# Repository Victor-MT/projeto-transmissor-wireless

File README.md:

# Projeto Transmissor Wireless

### Sobre o projeto

O projeto em questão foi desenvolvido  com intuito de resolver um desafio proposto em um processo seletivo. A proposta é comunicar dois dispositivos utilizando tecnologia sem fio ou "wireless".
 
Considerando todos os aspectos  do desenvolvimento de uma solução tecnológica, o projeto foi dividido em etapas como definição de requisitos, desenvolvimento de hardware, software e produto final. Todas essas fases, embora pareçam seguir uma ordem em cadeia, foram desenvolvidas de forma iterativa e isso resultou em uma solução que atende todos requisitos solicitados. 

### Sumário
- [Definição de Requisitos](https://github.com/Victor-MT/projeto-transmissor-wireless#defini%C3%A7%C3%A3o-de-requisitos)
- [Arquitetura](https://github.com/Victor-MT/projeto-transmissor-wireless#arquitetura)
- [Hardware](https://github.com/Victor-MT/projeto-transmissor-wireless#hardware)
- [Firmware](https://github.com/Victor-MT/projeto-transmissor-wireless#firmware)
- [Produto Final](https://github.com/Victor-MT/projeto-transmissor-wireless#produto-final)
- [Conclusão](https://github.com/Victor-MT/projeto-transmissor-wireless#conclus%C3%A3o)
- [Referências](https://github.com/Victor-MT/projeto-transmissor-wireless#refer%C3%AAncias)

## |Definição de Requisitos
Os requisitos definidos pelo cliente, nesse caso, o documento de especificação do projeto, foram: 
- Comunicar dois dispositivos, usando uma arquitetura integralmente sem fio em um range de 100 metros em espaço aberto. 
- Enviar um arquivo de 500kB 
- Componentes utilizados de fácil acesso ( disponíveis no mercado)
- Interface simples de operar 
- Pelo menos um dispositivo utilizando bateria
- Pensar na case do dispositivos (produto final) 

#### Ferramentas utilizadas :
Arduino IDE, KiCad software

## |Arquitetura
Para essa primeira versão que tem como fim uma prova de conceito (POC), a arquitetura escolhida para esse projeto foi, basicamente, um microcontrolador conectado a um transmissor e um microcontrolador conectado a um receptor com a possibilidade de enviar as informações recebidas para outro dispositivo via serial. Essa arquitetura corresponde ao tipo de comunicação simplex com um transmissor e um receptor.

#### Arquitetura proposta

## |Hardware
Baseado na premissa da disponibilidade de mercado, foi selecionado como microcontrolador o arduino nano (chip ATMega328P) e o transmissor nRF24L01 por sua alta disponibilidade e preços relativamente baixos. Segundo o próprio [datasheet](https://www.alldatasheet.com/datasheet-pdf/pdf/1243924/ETC1/NRF24L01.html) do nRF24L01, ele possui um alcance de 100m em espaços abertos, sendo assim, atende ao principal requisito do projeto. Além disso, o transceptor em questão posssui mais 1 canal para se comunicar o que permite comunicações full-duplex. 

#### Arduino | NRF24 spec

Com esses dois dispositivos escolhidos foi possível desenvolver o esquemático do sistema e a consequentemente a placa pcb.

#### Esquemático

Para o desenvolvimento da placa PCB foi utilizado o software KiCad.

#### PCB

[Formato da placa já desenvolvido para encaixar na case do protótipo.](https://github.com/Victor-MT/projeto-transmissor-wireless#produto-final)

#### PCB 3D

Coloquei os nomes dos dispositivos na placa 3D pois o KiCad não possui o modelo 3D dos componentes em questão, apenas as medidadas de referência. 

No caso acima para facilitar a configuração da placa e também deixar o protótipo aberto a futuras intervenções, foi utilizado a placa arduino nano e o módulo nRF24L01, porém durante o processo de confecção do produto real ambos podem ser substituídos por apenas o chip de cada módulo com apenas um circuito de proteção e assim diminuir ainda mais o custo do projeto.

A bateria do sistema foi escolhida baseada no consumo do mesmo que foi calculado em 31.3 mA. A bateria sugerida seria uma de 9V 250mAh ([bateria](https://www.amazon.com.br/Bateria-Recarreg%C3%A1vel-Blister-Elgin-Baterias/dp/B0754DF568/ref=asc_df_B0754DF568/?tag=googleshopp00-20&linkCode=df0&hvadid=379726667452&hvpos=&hvnetw=g&hvrand=8347384447641540275&hvpone=&hvptwo=&hvqmt=&hvdev=c&hvdvcmdl=&hvlocint=&hvlocphy=9100812&hvtargid=pla-809701102940&psc=1) e [conector](https://produto.mercadolivre.com.br/MLB-2114848124-clip-para-bateria-9v-capa-de-proteco-arduino-esp-nodemcu-_JM#position=2&search_layout=grid&type=item&tracking_id=4435f918-5bed-4264-9335-1ed655bfa6df)) e com isso a autonomia do projeto seria de aproximadamente 8 horas. 

## |Firmware
Para o desenvolvimento do firmware, por se tratar de dois dispositivos muito utilizados para prototipagem possuem diversas bibliotecas disponíveis, escolhemos utilizar a RF24, desenvolvida por [TMRh20](https://github.com/tmrh20/RF24/) que pode ser encontrada diretamente pelo gerenciador de bibliotecas na IDE do Arduino. 

No desenvolvimento  do firmware o principal desafio foi conseguir transportar um arquivo tão grande quanto 500kB já que a limitação do nRF24L01 é de 32 bytes por mensagem. Para solucionar o problema, o algoritmo desenvolvido divide a mensagem original em pequenos pedaços de 32 bytes de tamanho e depois o firmware do receptor remonta a mensagem. 

[Código do transmissor](https://github.com/Victor-MT/projeto-transmissor-wireless/tree/master/src/firmware/transmistter)
[Código do Receptor](https://github.com/Victor-MT/projeto-transmissor-wireless/tree/master/src/firmware/receiver)
## |Produto Final
Após a confecção da placa, foi desenvolvida uma case para proteger o sistema e tornar o produto mais apresentável para o cliente final poder manusear e acoplar onde for necessário. O formato octogonal foi escolhido por sua facilidade de encaixe em diversas posições e baixa complexidade de confecção, além de ser um formato agradável visualmente. 

#### Case

## |Conclusão
Após todas essas etapas, podemos concluir que todos requisitos foram cumpridos resultando em um produto de fácil confecção, acessível no mercado e de simples operação. Segue abaixo o custo relativo ao projeto, sem considerar o custo para produção da PCB nem fabricação da case que deperiam do fornecedor já que seriam personalizadas.

#### Custo do projeto

[Planilha de custos](https://github.com/Victor-MT/projeto-transmissor-wireless/tree/master/src/product)

### Melhorias

Este projeto teve o instituto de prototipar um sistema de comunicação wireless em uma semana, sendo assim, é evidente que ficam pendentes diversas melhorias que poderiam ser implementadas. Deixarei aqui algumas sugestões.

#### Upgrades Futuros: 
- Indicador LED alertando por código de cor se a mensagem foi enviada e/ou recebida;
- Mudança de protocolo para full-duplex;
- Melhoria do firmware para feedback de resposta sobre a integridade da mensagem enviada pelo transmissor;
- Interface desktop para ler e exibir informações do receptor;
## |Referências

 - [Understanding Wireless Range Calculations](https://www.electronicdesign.com/technologies/communications/article/21796484/understanding-wireless-range-calculations)
 - [About nRF24L01](https://howtomechatronics.com/tutorials/arduino/arduino-wireless-communication-nrf24l01-tutorial/)
 - [Library Documentation](https://nrf24.github.io/RF24/)
 - [nRF24L01 datasheet](https://www.alldatasheet.com/datasheet-pdf/pdf/1243924/ETC1/NRF24L01.html)
 - [Modos de transmissão](https://www.canalti.com.br/redes-de-computadores/modos-de-transmissao-de-dados-simplex-half-duplex-full-duplex/)

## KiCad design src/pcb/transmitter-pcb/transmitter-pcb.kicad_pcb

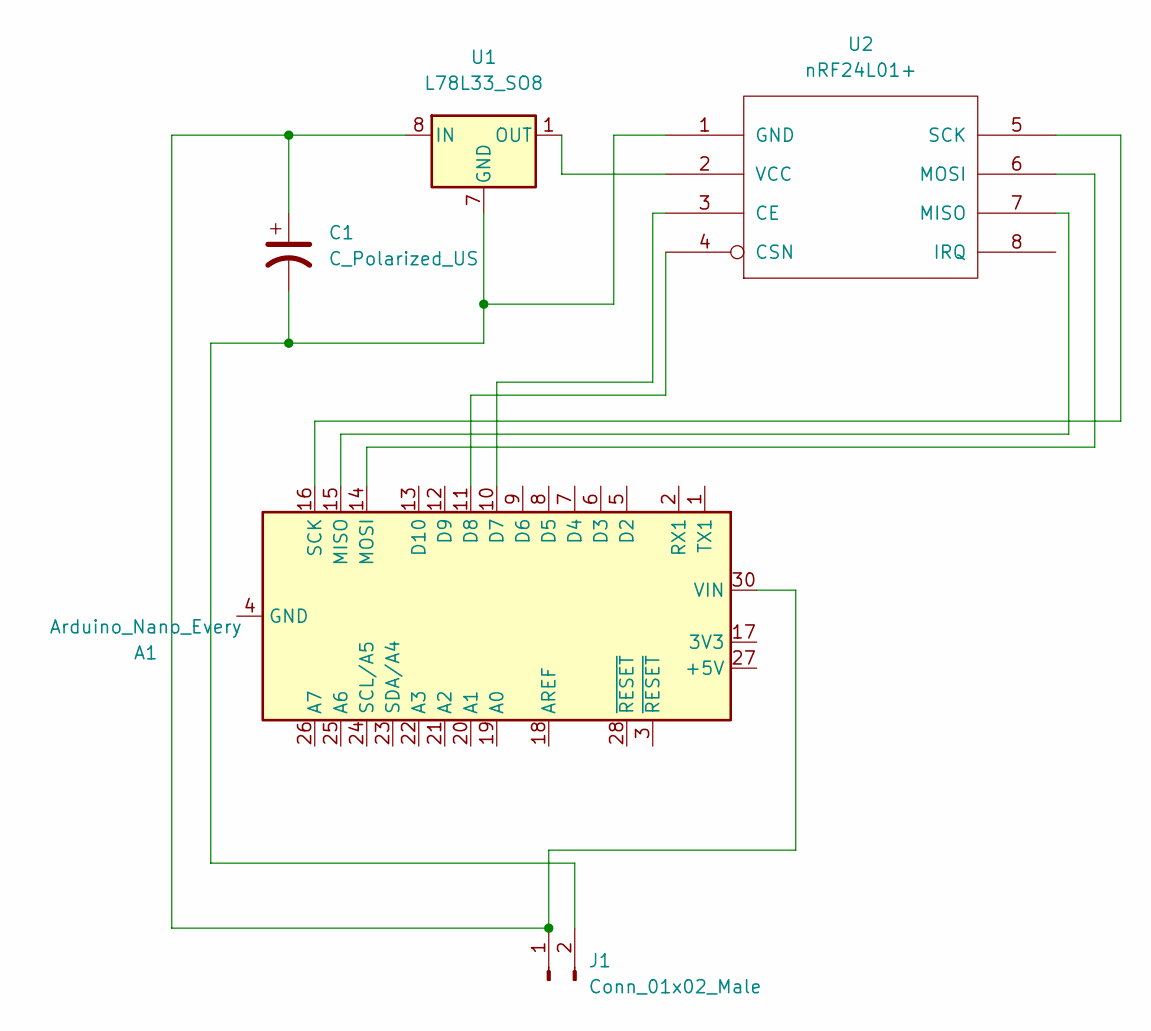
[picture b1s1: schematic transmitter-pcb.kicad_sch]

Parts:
A1: Arduino_Nano_Every; Arduino_Nano
C1: C_Polarized_US; CP_Elec_3x5.3
J1: Conn_01x02_Male; SolderWire-0.1sqmm_1x02_P3.6mm_D0.4mm_OD1mm
U1: L78L33_SO8; SOIC-8_3.9x4.9mm_P1.27mm
U2: nRF24L01+; nRF24L01_Breakout

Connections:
unnamed: A1.10 (D7), U2.3 (CE)
unnamed: A1.11 (D8), U2.4 (CSN)
unnamed: A1.14 (MOSI), U2.6 (MOSI)
unnamed: A1.15 (MISO), U2.7 (MISO)
unnamed: A1.16 (SCK), U2.5 (SCK)
unnamed: A1.4 (GND), A1.29 (GND)
unnamed: A1.30 (VIN), C1.1, J1.1, U1.8 (IN)
unnamed: C1.2, J1.2, U1.2 (GND), U1.3 (GND), U1.6 (GND), U1.7 (GND), U2.1 (GND)
unnamed: U1.1 (OUT), U2.2 (VCC)

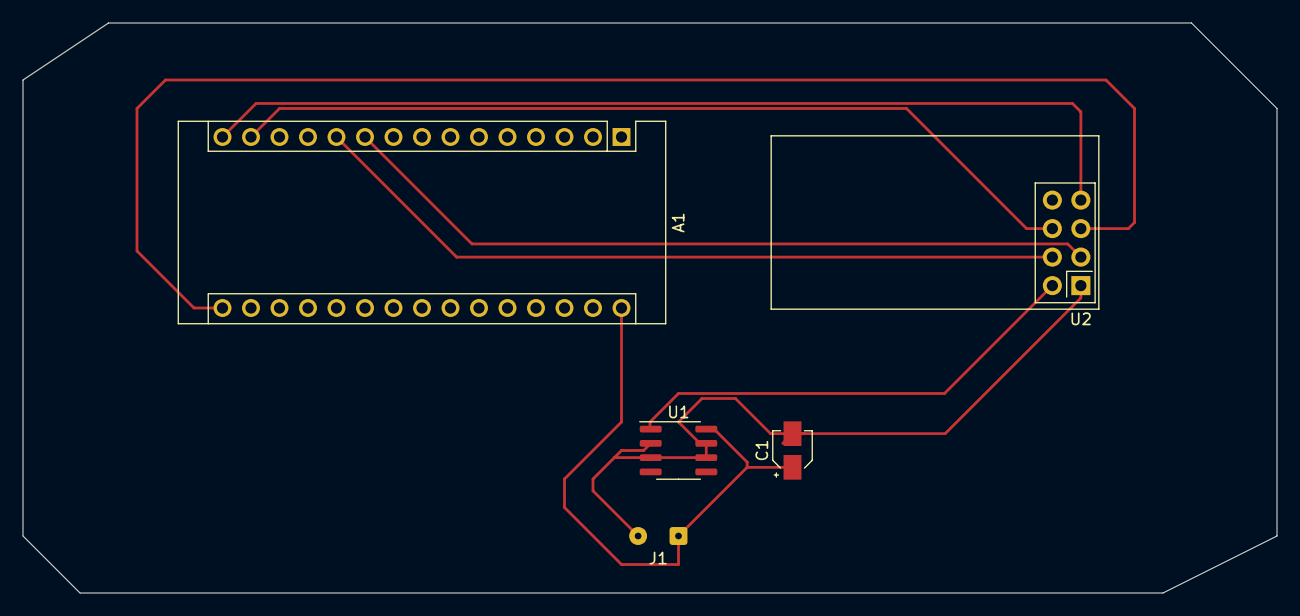
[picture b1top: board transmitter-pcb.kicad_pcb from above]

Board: 2 copper layers, 111.8 x 50.8 mm, 5 parts (0 on the bottom side), 9 nets.

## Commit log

2022-06-16 adding new info
2022-06-16 adding tractian logo
2022-06-16 case update
2022-06-16 custos
2022-06-16 last update
